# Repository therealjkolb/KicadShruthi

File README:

# **About this project** 

Shruthi-1, a digital/analog hybrid MIDI monosynth.

This project is a port of the Shruthi-1 Design into Kicad for current manufacturing, as well as addressing component obsolecence within the design.

Primary goal of the project is to take the exiting Eagle based design files and move them to Kicad. The project is to build the Digital XT control board as well
as the SMR4mk-II filter board only.

Inherited files that are not to be remanufactured removed for cleanliness, but design files relevant to the Digital XT and the SMR4mk-II are being retained.

Current Modifier: Jake Kolb (therealjkolb@gmail.com).

Original developer: Emilie Gillet (emilie.o.gillet@gmail.com)

# **Firmware Changes** 
- 3-17-2024 -- Will Kolb(wfkolb@gmail.com)
    - Changed debounce settings to add stability in ui.cc
    - Determined that building with avr-gcc 4.3.3 is the **ONLY** way to have successful page navigation. (Added a comment to editor.cc to show the failure point for other compilers)
    - Updated dsp/Makefile to point to the proper mcu (644p)

# **Code/Asset Licenses** 

The firmware is (still) released under a GPL3.0 license. It includes a
reimplementation of the formant synthesis algorithm used in Peter Knight's
Cantarino speech synthesizer.

The PCB layouts and schematics (in /hardware/shruthi/design/pcb)
are released under a Creative Commons cc-by-sa 3.0 license 

SMR4_MkII_V03 Filter board and the Digital XT filter board included, both ported from the orignal design files in Eagle to Kicad 6.

Additional footprint and rounting updates made on the SMR4_MKII filter board for manufacturability.

Documentation, analyses, simulations and 3D models are released under a
Creative Commons cc-by-sa 3.0 license.

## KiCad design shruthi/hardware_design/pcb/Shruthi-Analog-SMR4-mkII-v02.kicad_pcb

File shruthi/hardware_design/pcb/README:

PCB art (not used on these boards as of April 2023):
- "saraswati" by Francois Barbut.
- "peacock_face" by Emilie Gillet.
- "radha" by Emilie Gillet.

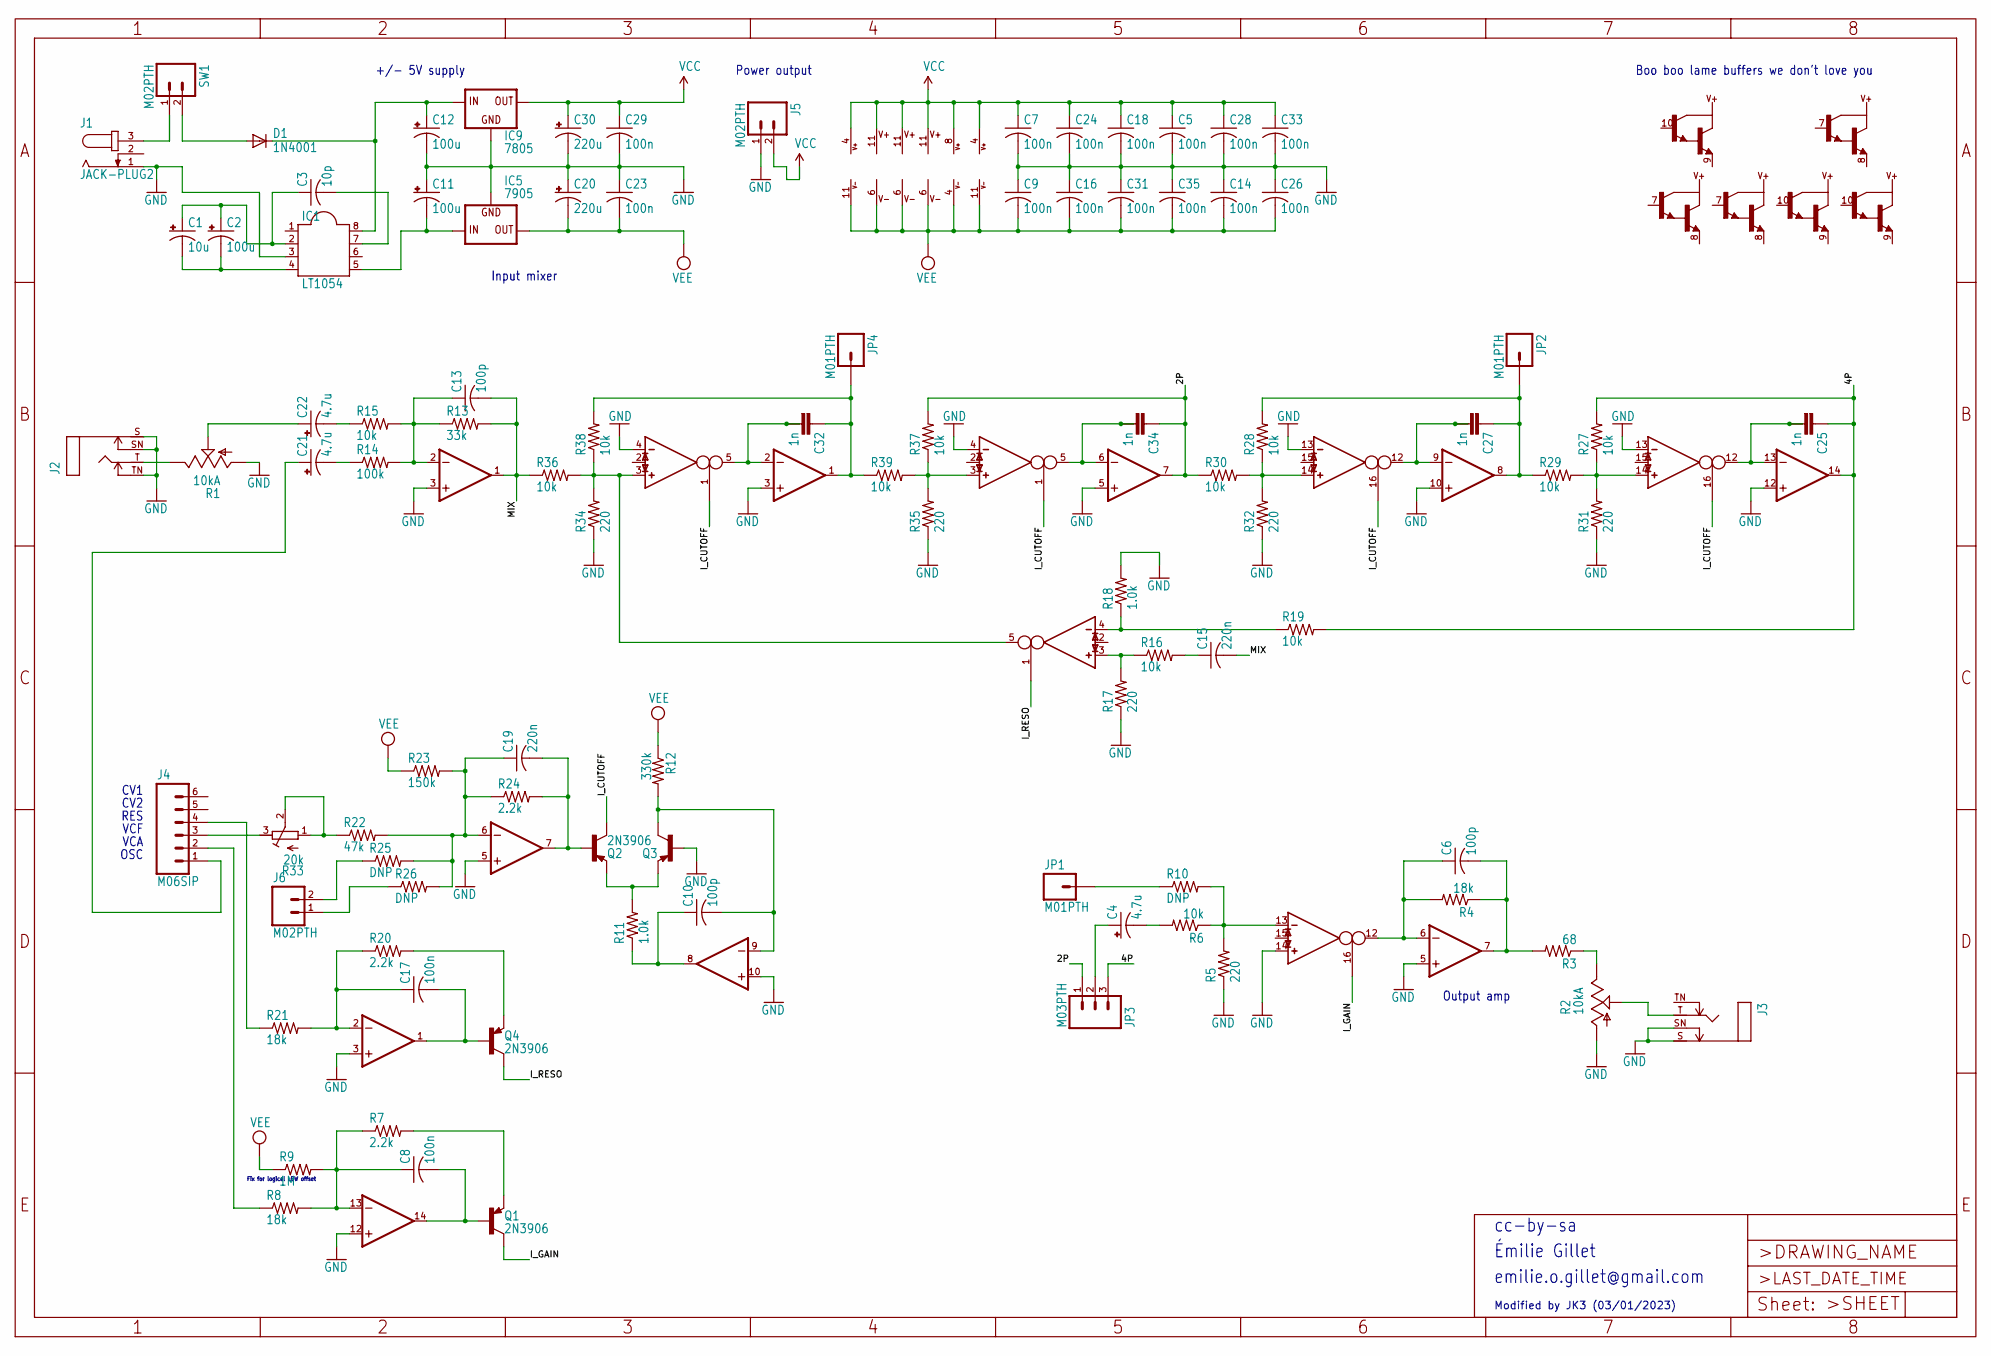
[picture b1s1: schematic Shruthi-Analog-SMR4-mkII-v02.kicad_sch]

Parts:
C1: 10u; E2,5-5
C2: 100u; E2,5-6
C3: 10p; C025-025X050
C4, C21, C22: 4.7u; E2,5-6
C5, C7, C8, C9, C14, C16, C17, C18, C23, C24, C26, C28, C29, C31, C33, C35: 100n; C025-025X050
C6, C10, C13: 100p; C025-025X050
C11, C12: 100u; E2,5-7
C15, C19: 220n; C025-025X050
C20, C30: 220u; E5-10,5
C25, C27, C32, C34: 1n; C2.5_5-2
D1: 1N4001; DO41-10
IC1: LT1054; DIL08
IC2: TL072P; DIL08
IC3, IC6, IC8: LM13700N; DIL16
IC4, IC7: TL074P; DIL14
IC5: 7905; 79XXS
IC9: 7805; 78XXS
J1: JACK-PLUG2; SPC4078_BIG_HOLES
J2, J3: MONOSWS; NMJ4HC-S
J4: M06SIP; 1X06
J5, J6: M02PTH; 1X02
JP1, JP2, JP4: M01PTH; 1X01
JP3: M03PTH; 1X03
Q1, Q2, Q3, Q4: 2N3906; TO92-
R1, R2: 10kA; CABLE_POT_6MM
R3: 68; 0204_7
R4, R8, R21: 18k; 0204_7
R5, R17, R31, R32, R34, R35: 220; 0204_7
R6, R15, R16, R19, R27, R28, R29, R30, R36, R37, R38, R39: 10k; 0204_7
R7, R20, R24: 2.2k; 0204_7
R9: 1M; 0204_7
R10, R25, R26: DNP; 0204V
R11, R18: 1.0k; 0204_7
R12: 330k; 0204_7
R13: 33k; 0204_7
R14: 100k; 0204_7
R22: 47k; 0204_7
R23: 150k; 0204_7
R33: 20k; RTRIM3296X
SW1: M02PTH; 1X02

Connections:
/2P: C34.1, IC7.7 (OUT), JP3.1, R30.1, R37.2
/4P: C25.1, IC7.14 (OUT), JP3.3, R19.2, R27.2
/I_CUTOFF: IC6.1 (I_BIAS), IC6.16 (I_BIAS), IC8.1 (I_BIAS), IC8.16 (I_BIAS), Q2.1 (C)
/I_GAIN: IC3.16 (I_BIAS), Q1.1 (C)
/I_RESO: IC3.1 (I_BIAS), Q4.1 (C)
/MIX: C13.2, C15.2, IC2.1 (OUT), R13.2, R36.1
GND: C5.2, C7.2, C9.1, C11.+, C12.-, C14.1, C16.1, C18.2, C20.+, C23.1, C24.2, C26.1, C28.2, C29.2, C30.-, C31.1, C33.2, C35.1, IC1.3, IC2.3 (+IN), IC2.5 (+IN), IC3.14 (IN_P), IC4.3 (+IN), IC4.5 (+IN), IC4.10 (+IN), IC4.12 (+IN), IC5.GND, IC6.4 (IN_N), IC6.13 (IN_N), IC7.3 (+IN), IC7.5 (+IN), IC7.10 (+IN), IC7.12 (+IN), IC8.4 (IN_N), IC8.13 (IN_N), IC9.GND, J1.1, J2.S, J2.SN, J2.TN, J3.S, J3.SN, J5.1, Q3.2 (B), R1.A, R2.A, R5.1, R17.1, R18.2, R31.1, R32.1, R34.1, R35.1
unnamed: C1.+, C2.+, C3.1, IC1.2
unnamed: C1.-, C2.-, IC1.4
unnamed: C3.2, IC1.7
unnamed: C4.+, JP3.2
unnamed: C4.-, R6.2
unnamed: C6.1, IC2.6 (-IN), IC3.12 (OUT), R4.2
unnamed: C6.2, IC2.7 (OUT), R3.2, R4.1
unnamed: C8.1, IC4.13 (-IN), R7.1, R8.2, R9.2
unnamed: C8.2, IC4.14 (OUT), Q1.2 (B)
unnamed: C10.1, IC4.8 (OUT), R11.1
unnamed: C10.2, IC4.9 (-IN), Q3.1 (C), R12.2
unnamed: C11.-, IC1.5, IC5.IN
unnamed: C12.+, D1.C, IC1.8, IC9.IN
unnamed: C13.1, IC2.2 (-IN), R13.1, R14.2, R15.2
unnamed: C15.1, R16.2
unnamed: C17.1, IC4.2 (-IN), R20.1, R21.2
unnamed: C17.2, IC4.1 (OUT), Q4.2 (B)
unnamed: C19.1, IC4.6 (-IN), R22.2, R23.2, R24.1, R25.2, R26.2
unnamed: C19.2, IC4.7 (OUT), Q2.2 (B), R24.2
unnamed: C21.+, J4.1
unnamed: C21.-, R14.1
unnamed: C22.+, R1.S
unnamed: C22.-, R15.1
unnamed: C25.2, C25.3, IC6.12 (OUT), IC7.13 (-IN)
unnamed: C27.1, IC7.8 (OUT), JP2.1, R28.2, R29.1
unnamed: C27.2, C27.3, IC7.9 (-IN), IC8.12 (OUT)
unnamed: C32.1, IC7.1 (OUT), JP4.1, R38.2, R39.1
unnamed: C32.2, C32.3, IC6.5 (OUT), IC7.2 (-IN)
unnamed: C34.2, C34.3, IC7.6 (-IN), IC8.5 (OUT)
unnamed: D1.A, SW1.2
unnamed: IC3.3 (IN_P), R16.1, R17.2
unnamed: IC3.4 (IN_N), R18.1, R19.1
unnamed: IC3.5 (OUT), IC6.3 (IN_P), R34.2, R36.2, R38.1
unnamed: IC3.13 (IN_N), R5.2, R6.1, R10.2
unnamed: IC6.14 (IN_P), R27.1, R29.2, R31.2
unnamed: IC8.3 (IN_P), R35.2, R37.1, R39.2
unnamed: IC8.14 (IN_P), R28.1, R30.2, R32.2
unnamed: J1.3, SW1.1
unnamed: J2.T, R1.E
unnamed: J3.T, R2.S
unnamed: J4.2, R8.1
unnamed: J4.3, R33.3 (A)
unnamed: J4.4, R21.1
unnamed: J6.1, R26.1
unnamed: J6.2, R25.1
unnamed: JP1.1, R10.1
unnamed: Q1.3 (E), R7.2
unnamed: Q2.3 (E), Q3.3 (E), R11.2
unnamed: Q4.3 (E), R20.2
unnamed: R2.E, R3.1
unnamed: R22.1, R33.1 (E), R33.2 (S)
VCC: C5.1, C7.1, C18.1, C24.1, C28.1, C29.1, C30.+, C33.1, IC2.8 (V+), IC3.11 (V+), IC4.4 (V+), IC6.11 (V+), IC7.4 (V+), IC8.11 (V+), IC9.OUT, J5.2
VEE: C9.2, C14.2, C16.2, C20.-, C23.2, C26.2, C31.2, C35.2, IC2.4 (V-), IC3.6 (V-), IC4.11 (V-), IC5.OUT, IC6.6 (V-), IC7.11 (V-), IC8.6 (V-), R9.1, R12.1, R23.1

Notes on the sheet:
OSC
Boo boo lame buffers we don't love you
Fix for logical LOW offset
cc-by-sa
+/- 5V supply
Modified by JK3 (03/01/2023)
Power output
Output amp
Input mixer
CV1
Émilie Gillet
emilie.o.gillet@gmail.com
RES
VCF
CV2
VCA

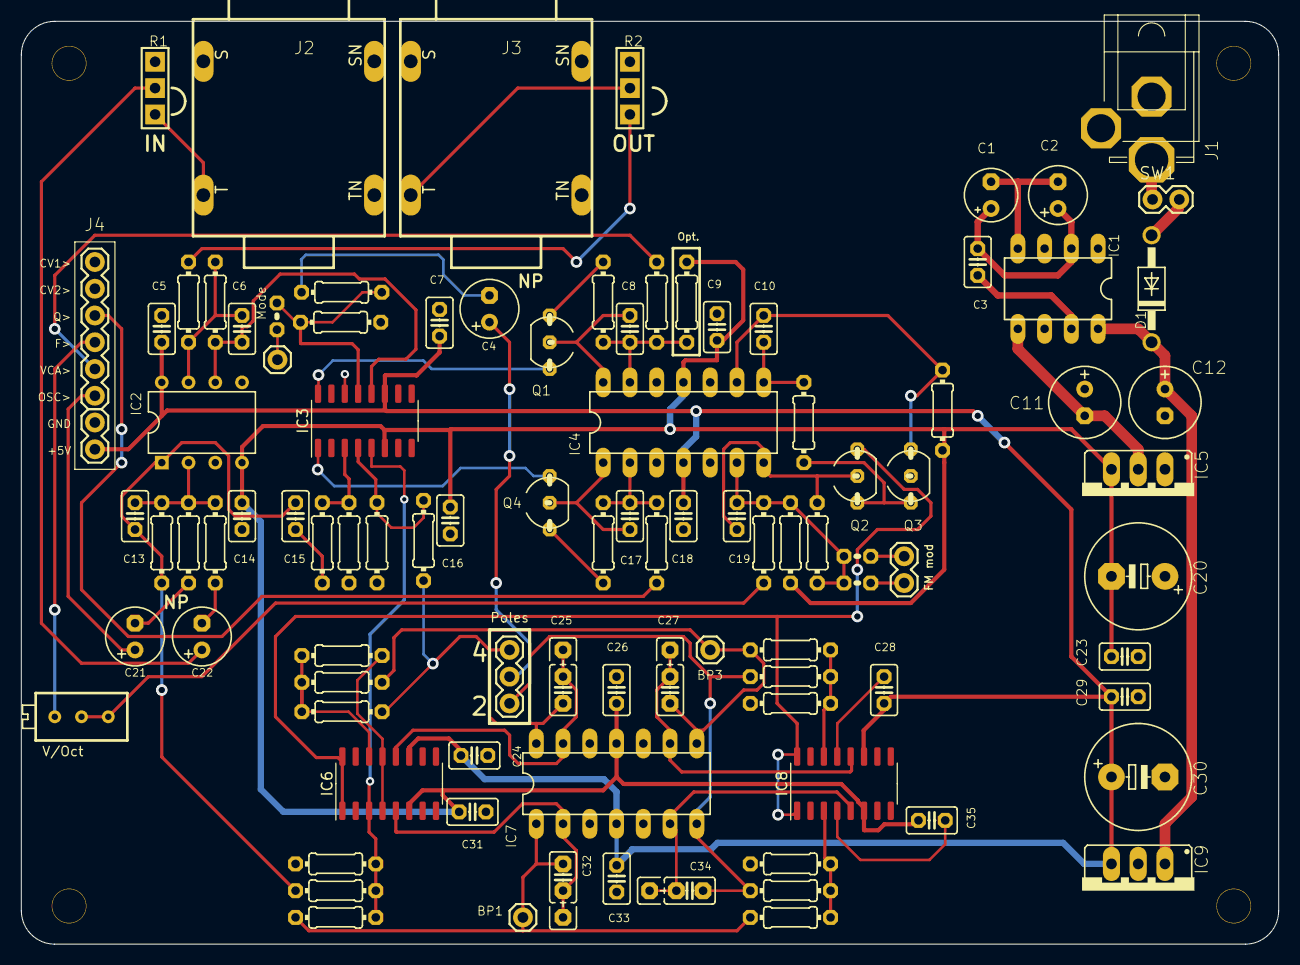
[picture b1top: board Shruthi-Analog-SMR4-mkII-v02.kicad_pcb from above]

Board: 2 copper layers, 119.4 x 87.6 mm, 99 parts (0 on the bottom side), 60 nets.

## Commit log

2023-07-22 Update the submodules to https over git protocol
2023-10-08 Added a script to combine build steps
2024-02-23 Minor changes to firmware revision and SN to prove life.
2024-03-17 Cleaned up readme, changed some debouce settings, removed willbuild functionality
2024-05-12 Updated Hardware design files to be usable after cloning repo. Added structures within the /pcb directory for Digital XT board and the SMR4-mkII-v02 board.
